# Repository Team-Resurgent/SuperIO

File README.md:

SuperIO

This is a Work In Progress version of https://github.com/XboxDev/serial-usb-adapter.

I started this so that mnanufacture would be cheaper having components on one side.

There maybe a mistake on the BOM / crystal

Ultimately I would like to merge with the xenium chip / add maybe other useful features.

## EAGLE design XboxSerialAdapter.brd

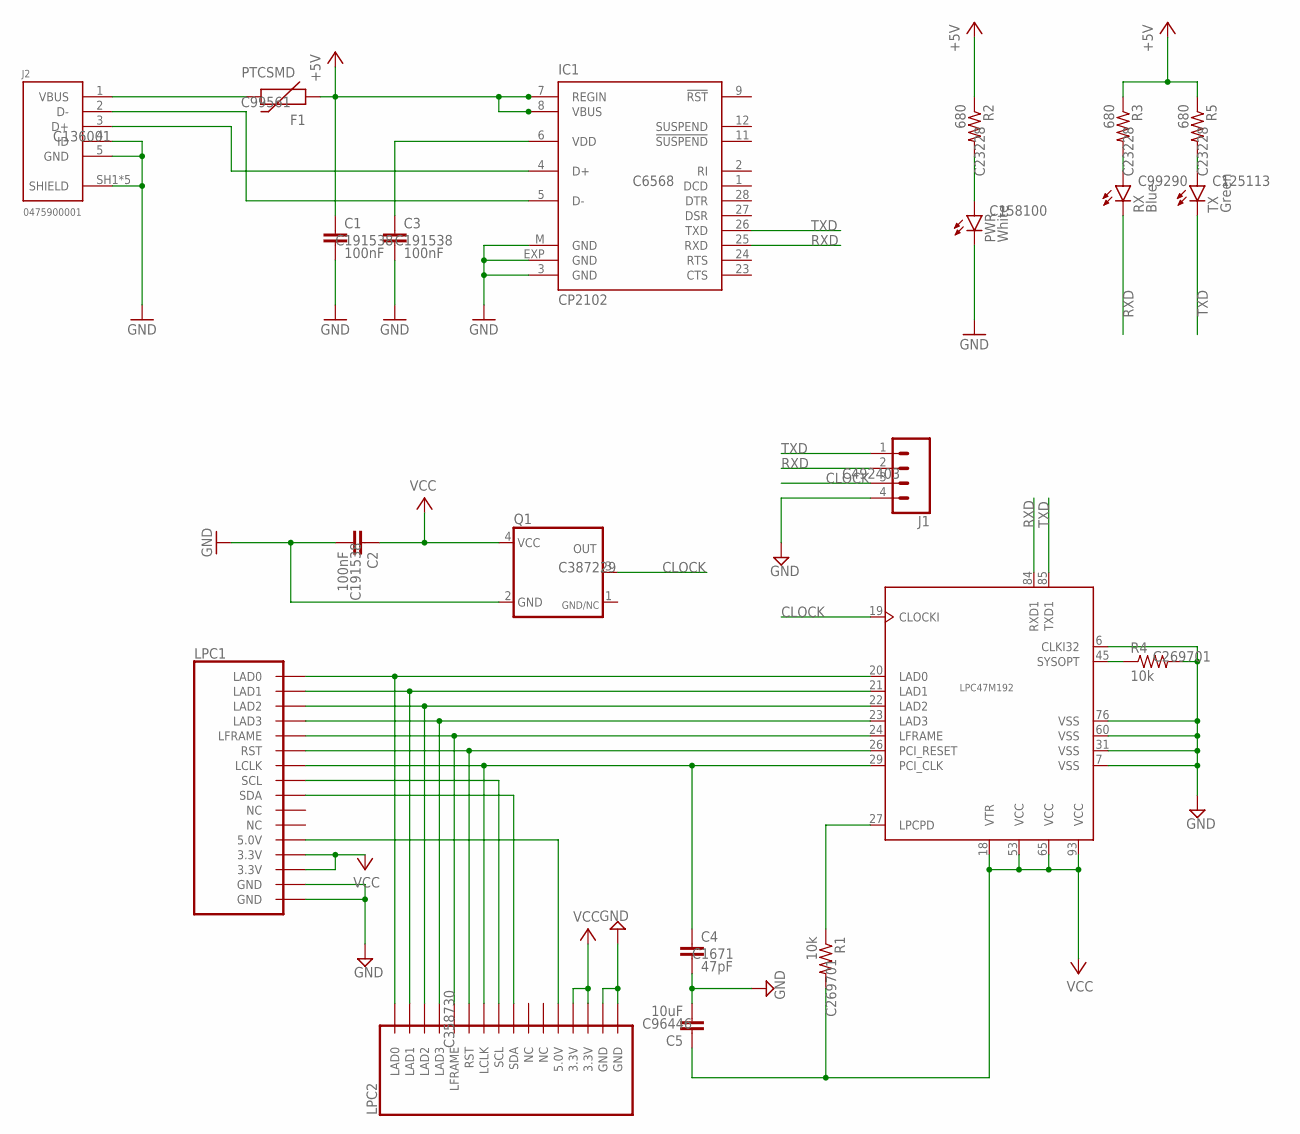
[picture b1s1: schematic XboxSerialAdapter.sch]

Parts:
C1, C2, C3: 100nF; 0603-CAP; LCSC_PART C191538
C4: 47pF; 0603-CAP; LCSC_PART C1671
C5: 10uF; 0603-CAP; LCSC_PART C96446
F1: PTCSMD; PTC-1206; LCSC_PART C99561
IC1: CP2102; MLP28; LCSC_PART C6568
J1: CONN_04; 1X04; LCSC_PART C492403
J2: 0475900001; LCSC_PART C136001
LPC1: LPC_HEADERLPC_FEMALE; HDRVR16W64P254_2X8_1524X508X254B; LCSC_PART C492425
LPC2: LPC_HEADERLPC_FEMALE; HDRVR16W64P254_2X8_1524X508X254B; LCSC_PART C358730
PWR: White; CHIP-LED0603; LCSC_PART C158100
Q1: SCTF_C3872291; SCTF_C387229; LCSC_PART C387229
R1, R4: 10k; 0603-RES; LCSC_PART C269701
R2, R3, R5: 680; 0603-RES; LCSC_PART C23228
RX: Blue; CHIP-LED0603; LCSC_PART C99290
TX: Green; CHIP-LED0603; LCSC_PART C125113
U1: LPC47M192; QFP128

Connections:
5.0V: LPC1.6 (5.0V), LPC2.6 (5.0V)
+5V: C1.1, F1.1, IC1.7 (REGIN), IC1.8 (VBUS), R2.1, R3.1, R5.1
CLOCK: J1.3, Q1.3 (OUT), U1.19 (CLOCKI)
D+: IC1.4 (D+), J2.3 (D+)
D-: IC1.5 (D-), J2.2 (D-)
GND: C1.2, C2.2, C3.2, C4.2, C5.2, IC1.3 (GND), IC1.EXP (GND), IC1.M (GND), J1.4, J2.4 (ID), J2.5 (GND), J2.SH1 (SHIELD), J2.SH2 (SHIELD), J2.SH3 (SHIELD), J2.SH4 (SHIELD), J2.SH5 (SHIELD), LPC1.2 (GND), LPC1.12 (GND), LPC2.2 (GND), LPC2.12 (GND), PWR.C, Q1.2 (GND), R4.2, U1.6 (CLKI32), U1.7 (VSS), U1.31 (VSS), U1.60 (VSS), U1.76 (VSS)
GND/NC: Q1.1 (GND/NC)
LAD0: LPC1.11 (LAD0), LPC2.11 (LAD0), U1.20 (LAD0)
LAD1: LPC1.10 (LAD1), LPC2.10 (LAD1), U1.21 (LAD1)
LAD2: LPC1.8 (LAD2), LPC2.8 (LAD2), U1.22 (LAD2)
LAD3: LPC1.7 (LAD3), LPC2.7 (LAD3), U1.23 (LAD3)
LCLK: C4.1, LPC1.1 (LCLK), LPC2.1 (LCLK), U1.29 (PCI_CLK)
LFRAME: LPC1.3 (LFRAME), LPC2.3 (LFRAME), U1.24 (LFRAME)
unnamed: R4.1, U1.45 (SYSOPT)
unnamed: R5.2, TX.A
unnamed: R3.2, RX.A
unnamed: C3.1, IC1.6 (VDD)
unnamed: R1.1, U1.27 (LPCPD)
unnamed: PWR.A, R2.2
RST: LPC1.5 (RST), LPC2.5 (RST), U1.26 (PCI_RESET)
RXD: IC1.25 (RXD), J1.2, RX.C, U1.84 (RXD1)
SCL: LPC1.13 (SCL), LPC2.13 (SCL)
SDA: LPC1.14 (SDA), LPC2.14 (SDA)
TXD: IC1.26 (TXD), J1.1, TX.C, U1.85 (TXD1)
VBUS: F1.2, J2.1 (VBUS)
VCC: C2.1, C5.1, LPC1.9 (3.3V), LPC1.15 (3.3V), LPC2.9 (3.3V), LPC2.15 (3.3V), Q1.4 (VCC), R1.2, U1.18 (VTR), U1.53 (VCC), U1.65 (VCC), U1.93 (VCC)

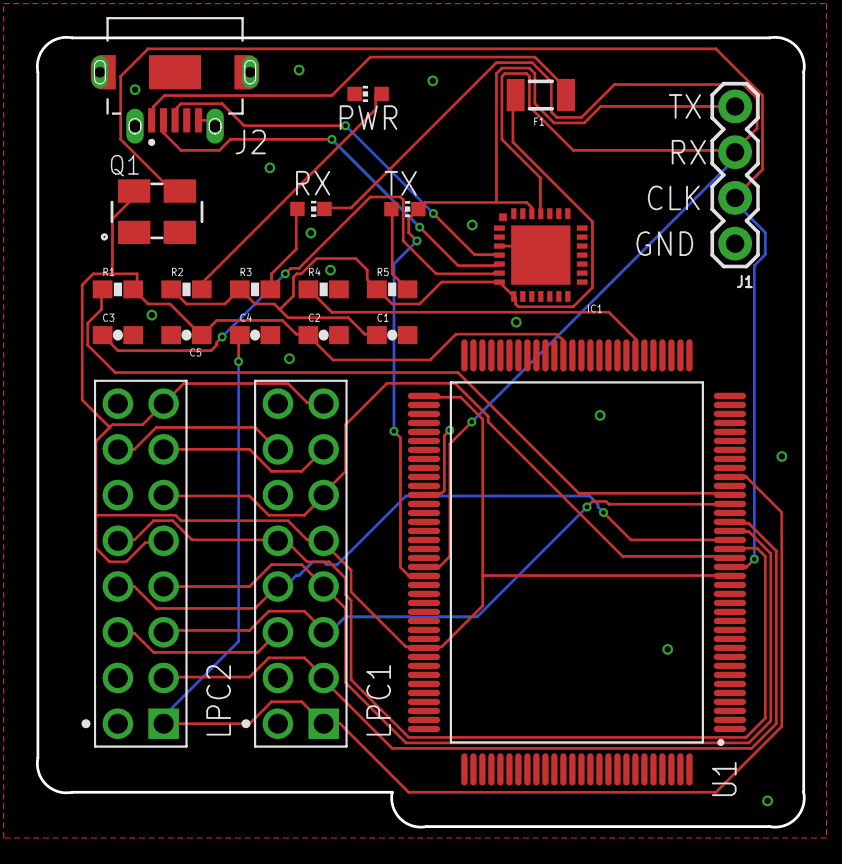
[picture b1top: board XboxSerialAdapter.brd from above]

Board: 2 copper layers, 42.6 x 43.9 mm, 21 parts (0 on the bottom side), 25 nets.

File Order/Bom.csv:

Comment,Designator,Footprint,LCSC Part #
10k,R1 R4,0603-RES,C269701
14.31818 oscillator,Q1,SMD5032-4P,C387229
10uF,C5,0603-CAP,C96446
47pF,C4,0603-CAP,C1671
100nF,C1 C2 C3,0603-CAP,C191538
680,R2 R3 R5,0603-RES,C23228
475900001,J2,475900001,C136001
Blue,RX,CHIP-LED0603,C99290
CP2102,IC1,MLP28,C6568
Green,TX,CHIP-LED0603,C72043
LPC47M192,U1,QFP128,
PTCSMD,F1,PTC-1206,C99561
White,PWR,CHIP-LED0603,C158100

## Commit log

2021-12-07 Update: added files
2021-12-07 Update: crystal
2021-12-07 Update: files

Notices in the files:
parts and their libraries:
SparkFun: Licensing: CC v3.0 Share-Alike You are welcome to use this library for commercial purposes.
SparkFun-Connectors: Licensing: Creative Commons ShareAlike 4.0 International - https://creativecommons.org/licenses/by-sa/4.0
